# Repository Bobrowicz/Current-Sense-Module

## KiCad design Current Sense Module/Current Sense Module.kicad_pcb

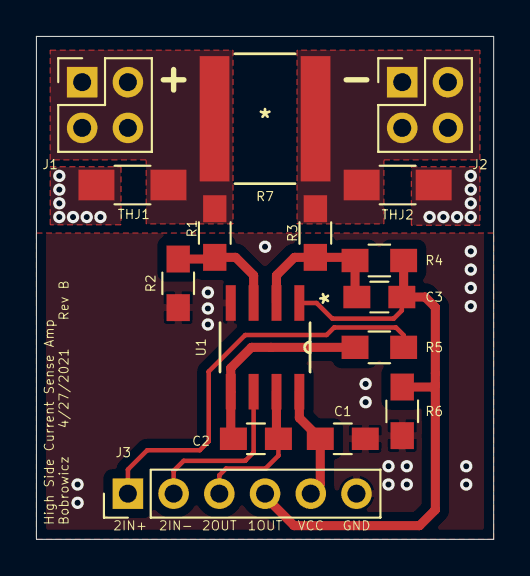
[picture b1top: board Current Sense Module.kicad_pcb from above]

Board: 2 copper layers, 25.4 x 27.9 mm, 16 parts (0 on the bottom side), 11 nets.

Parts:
C1: 0.1u; C_0805_HandSoldering
C2: 330p; C_0805_HandSoldering
C3: 0p; C_0805_HandSoldering
J1, J2: Conn_01x04_Male; Pin_Header_Straight_2x02_Pitch2.54mm
J3: Conn_01x06_Male; Pin_Header_Straight_1x06_Pitch2.54mm
R1, R3: 10k 0.1%; R_0805_HandSoldering
R2: 100k 0.1%; R_0805_HandSoldering
R4: 100k 0.1 %; R_0805_HandSoldering
R5: 10k; R_0805_HandSoldering
R6: 47k; R_0805_HandSoldering
R7: 0R1 0.5%; PCS2728DR1000ET
THJ1, THJ2: R; R_1206_HandSoldering
U1: OPA2990; TLC2272IDR

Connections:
/1IN+: R1.1, R2.2, U1.3
/1IN-: C3.2, R3.1, R4.2, U1.2
/1OUT: C3.1, J3.4, R4.1, R6.2, U1.1
/2IN+: J3.1, R5.2
/2IN-: J3.2, U1.6
/2OUT: C2.1, J3.3, U1.7
/Bus_Voltage: J1.1, J1.2, J1.3, J1.4, R1.2, R7.2, THJ1.1
/Load: J2.1, J2.2, J2.3, J2.4, R3.2, R7.1, THJ2.1
GND: C1.2, J3.6, R2.1, R6.1, THJ1.2, THJ2.2, U1.4
unnamed: C2.2, R5.1, U1.5
VCC: C1.1, J3.5, U1.8

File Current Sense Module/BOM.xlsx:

Reference | Quantity | Value | Footprint | MPN
R1 R3 | 2 | 10k | 0805 | ERA-6AEB103V
R2 R4 | 2 | 100k | 0805 | ERA-6AEB104V
R5 | 1 | 10k | 0805 | RNCP0805FTD10K0
R6 | 1 | 47k | 0805 | ERJ-6ENF4702V
R7 | 1 | 0R1 | 2827 | PCS2728DR1000ET
C1 | 1 | 100n | 0805 | C0805C104K3RACTU
C2 | 1 | 330p | 0805 | 885012007037
U1 | 1 | OPA2990 | 8-SOIC | OPA2990IDR
THJ1 THJ2 | 2 | Jumper | 1206 | THJP1206ABT1
J1 J2 | 1 | Conn Header | 0.254 | PR20205VBDN
J3 | 1 | Conn Header | 0.254 | PREC020SAAN-RC

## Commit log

2021-02-04 Initial Commit
    Schematic and beginning of PCB layout.
2021-02-05 Completed PCB layout
2021-02-08 PCB tweal
    Inverted pin headers and edited silk screen.
2021-03-23 Schematic component update
2021-04-16 removed fp-info-cache
2021-04-27 Rev B
    Added thermal jumpers. Brought out inputs of the second op-amp to header. Added BOM.

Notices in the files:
parts and their libraries:
Copyright 2016 Accelerated Designs. All rights reserved.
